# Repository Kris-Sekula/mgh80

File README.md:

# mgh80 - "The Arduino of the 80s"

This 5 chip Z80 single-board "computer", is a very simple Z80 based "controller" with 8255 for I/O plus a ["Z50Bus"](http://linc.no/products/z50bus/) expansion connector. I created it to kick-start my Z80 experiments - breadboarding is fun, but sometimes you want the basics to "just work" so you don't have to troubleshoot loose wires :) 

Features an option to use a local crystal-based oscillator or oscillator module. There is an onboard selector to choose between 27c256 EPROM and 28C256 EEPROM.

You can find more detailed project description on my website [mygeekyhobby.com](https://mygeekyhobby.com/2026/03/07/mgh-80-the-arduino-of-the-80s/)

Onboard address decoder:
* ROM at 0000h - 7FFFh
* RAM at 8000h - FFFFh
* IO at 00h (IOPortA)
* IO at 01h (IOPortB)
* IO at 02h (IOPortC)
* IO at 03h (Control)

A few solder jumpers allow disconnecting various onboard options (if you for example want to provide an external address decoder)... In the basic configuration you should link (with a solder blob) the following:
* JP1 - enable internal CLK source
* JP2 - enable internal IO(8255) address decoder
* JP3 - enable internal ROM address decoder
* JP4 - enable internal RAM address decoder
* JP7 - set 8255 reset pin to GND (bypass R5)
* JP8 - enable onboard LED for port A0 on the 8255
* JP9 - enable onboard IO_WR singal

Simple "blinky" program source (.asm) included and a compiled hex files (.hex) for 27C256 EPROM (or my EPROM emulator). It will toggle all lines of port A a few times a second.

In the "Monitor" folder, you will find sources for a monitor ROM — the bare-metal firmware that boots up, gives you a command prompt, and lets you inspect/modify memory, set breakpoints, and run programs.

Get your PCBs from [PCBWAY](https://www.pcbway.com/project/shareproject/mgh80___the_Arduino_of_the_80s__simple_z80_based__microcontroller____sbc_.html)

A few component kits are listed on [eBay](https://www.ebay.com/sch/avr4sale/m.html?_nkw=&_armrs=1&_ipg=&_from=)

If you found this helpful and you like the work I do, why not buy me a coffee? Thanks! :)

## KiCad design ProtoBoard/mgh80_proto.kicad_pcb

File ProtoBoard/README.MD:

This is a companion board to mgh80. It extends the I/O connections and the z80Bus to a prototyping board giving you a larger "experiments area".

All signals are marked with a label.

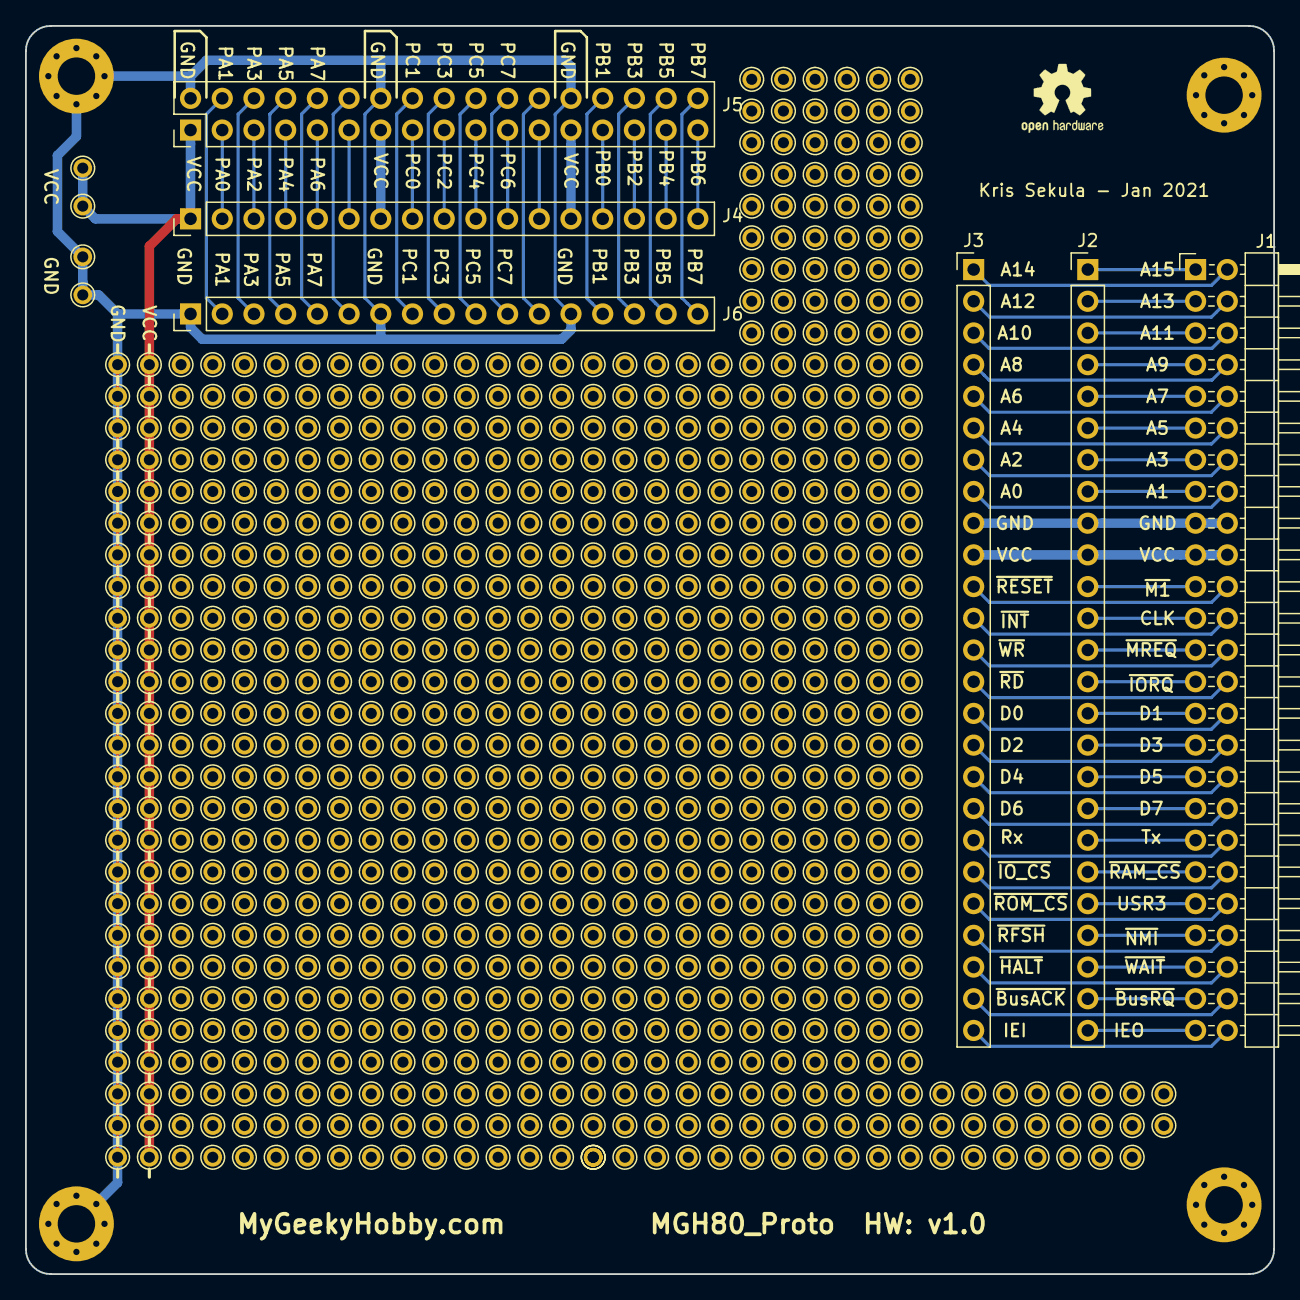
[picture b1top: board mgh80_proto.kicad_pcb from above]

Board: 2 copper layers, 100.0 x 100.0 mm, 14 parts (0 on the bottom side), 76 nets.

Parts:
H1, H2, H3, H4: MountingHole_Pad; MountingHole_3mm_Pad_Via
J1: Z80Bus; PinHeader_2x25_P2.54mm_Horizontal
J2, J3: Conn_01x25; PinHeader_1x25_P2.54mm_Vertical
J4, J6: Conn_01x17; PinHeader_1x17_P2.54mm_Vertical
J5: Conn_02x15_Odd_Even; PinHeader_2x17_P2.54mm_Vertical
TP1, TP1#2: 5V VCC; TestPoint_THTPad_D1.5mm_Drill0.7mm
TP2, TP2#2: GND; TestPoint_THTPad_D1.5mm_Drill0.7mm

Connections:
/A0: J1.16, J3.8
/A1: J1.15, J2.8
/A2: J1.14, J3.7
/A3: J1.13, J2.7
/A4: J1.12, J3.6
/A5: J1.11, J2.6
/A6: J1.10, J3.5
/A7: J1.9, J2.5
/A8: J1.8, J3.4
/A9: J1.7, J2.4
/A10: J1.6, J3.3
/A11: J1.5, J2.3
/A12: J1.4, J3.2
/A13: J1.3, J2.2
/A14: J1.2, J3.1
/A15: J1.1, J2.1
/CLK: J1.23, J2.12
/D0: J1.30, J3.15
/D1: J1.29, J2.15
/D2: J1.32, J3.16
/D3: J1.31, J2.16
/D4: J1.34, J3.17
/D5: J1.33, J2.17
/D6: J1.36, J3.18
/D7: J1.35, J2.18
/PA0: J4.2, J5.3
/PA1: J5.4, J6.2
/PA2: J4.3, J5.5
/PA3: J5.6, J6.3
/PA4: J4.4, J5.7
/PA5: J5.8, J6.4
/PA6: J4.5, J5.9
/PA7: J5.10, J6.5
/PB0: J4.14, J5.27
/PB1: J5.28, J6.14
/PB2: J4.15, J5.29
/PB3: J5.30, J6.15
/PB4: J4.16, J5.31
/PB5: J5.32, J6.16
/PB6: J4.17, J5.33
/PB7: J5.34, J6.17
/PC0: J4.8, J5.15
/PC1: J5.16, J6.8
/PC2: J4.9, J5.17
/PC3: J5.18, J6.9
/PC4: J4.10, J5.19
/PC5: J5.20, J6.10
/PC6: J4.11, J5.21
/PC7: J5.22, J6.11
/~BusACK: J1.48, J3.24
/~BusRQ: J1.47, J2.24
/~HALT: J1.46, J3.23
/~INT: J1.24, J3.12
/~IORQ: J1.27, J2.14
/~IO_CS: J1.40, J3.20
/~M1: J1.21, J2.11
/~MREQ: J1.25, J2.13
/~NMI: J1.43, J2.22
/~RAM_CS: J1.39, J2.20
/~RD: J1.28, J3.14
/~RESET: J1.22, J3.11
/~RFSH: J1.44, J3.22
/~ROM_CS: J1.42, J3.21
/~WR: J1.26, J3.13
/~Wait: J1.45, J2.23
GND: H1.1, H2.1, H3.1, H4.1, J1.17, J1.18, J2.9, J3.9, J5.2, J5.14, J5.26, J6.1, J6.7, J6.13, TP2.1, TP2#2.1
unnamed: J1.37, J2.19
unnamed: J1.38, J3.19
unnamed: J1.41, J2.21
unnamed: J1.49, J2.25
unnamed: J1.50, J3.25
unnamed: J4.6, J5.11
unnamed: J4.12, J5.23
unnamed: J5.12, J6.6
unnamed: J5.24, J6.12
VCC: J1.19, J1.20, J2.10, J3.10, J4.1, J4.7, J4.13, J5.1, J5.13, J5.25, TP1.1, TP1#2.1

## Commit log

2020-10-12 Added schematic diagram.
2020-10-15 Fixed Reset
2020-11-15 Added sources for v1.0
2020-11-15 Blinky sources added
2020-11-29 3d rendering of HW 1.1 added
2020-12-27 Added HW v1.2 sources
2020-12-27 Added v1.2 schematic in PDF
2021-01-02 Added KiCad sources for v1.3
2021-01-03 added Gerbers for v1.3
2021-01-03 Added v1.3 PCB render
2021-01-14 Create Gerbers
2021-03-09 Added assembly instructions for the DIY kit
2021-04-17 HW ver 1.4 source files added
2021-04-17 Schematic hw 1.4 added
2021-05-22 Update example - blink on PA (including PA0)
2021-10-17 Schematic v1.5 added
2021-10-17 Added assembly instructions for Hw 1.5
2021-10-17 Create Serial_ExpansionBoard
2022-08-29 Serial board instructions added
2024-07-17 PCB mod instructions for mgh80 compatibility
2026-02-11 Updated instructions
    Removed the mention of closing JP6 - as this would cause a shot of the output of the NAND gate.
2026-03-28 Add simple "monitor" with built in BASIC support and bit-banged serial
2026-03-28 Updated utility instructions
2026-03-28 Updated instructions
2026-03-28 Added design files for v1.7 and updated instructions
2026-03-28 Added 1.7 pdf
